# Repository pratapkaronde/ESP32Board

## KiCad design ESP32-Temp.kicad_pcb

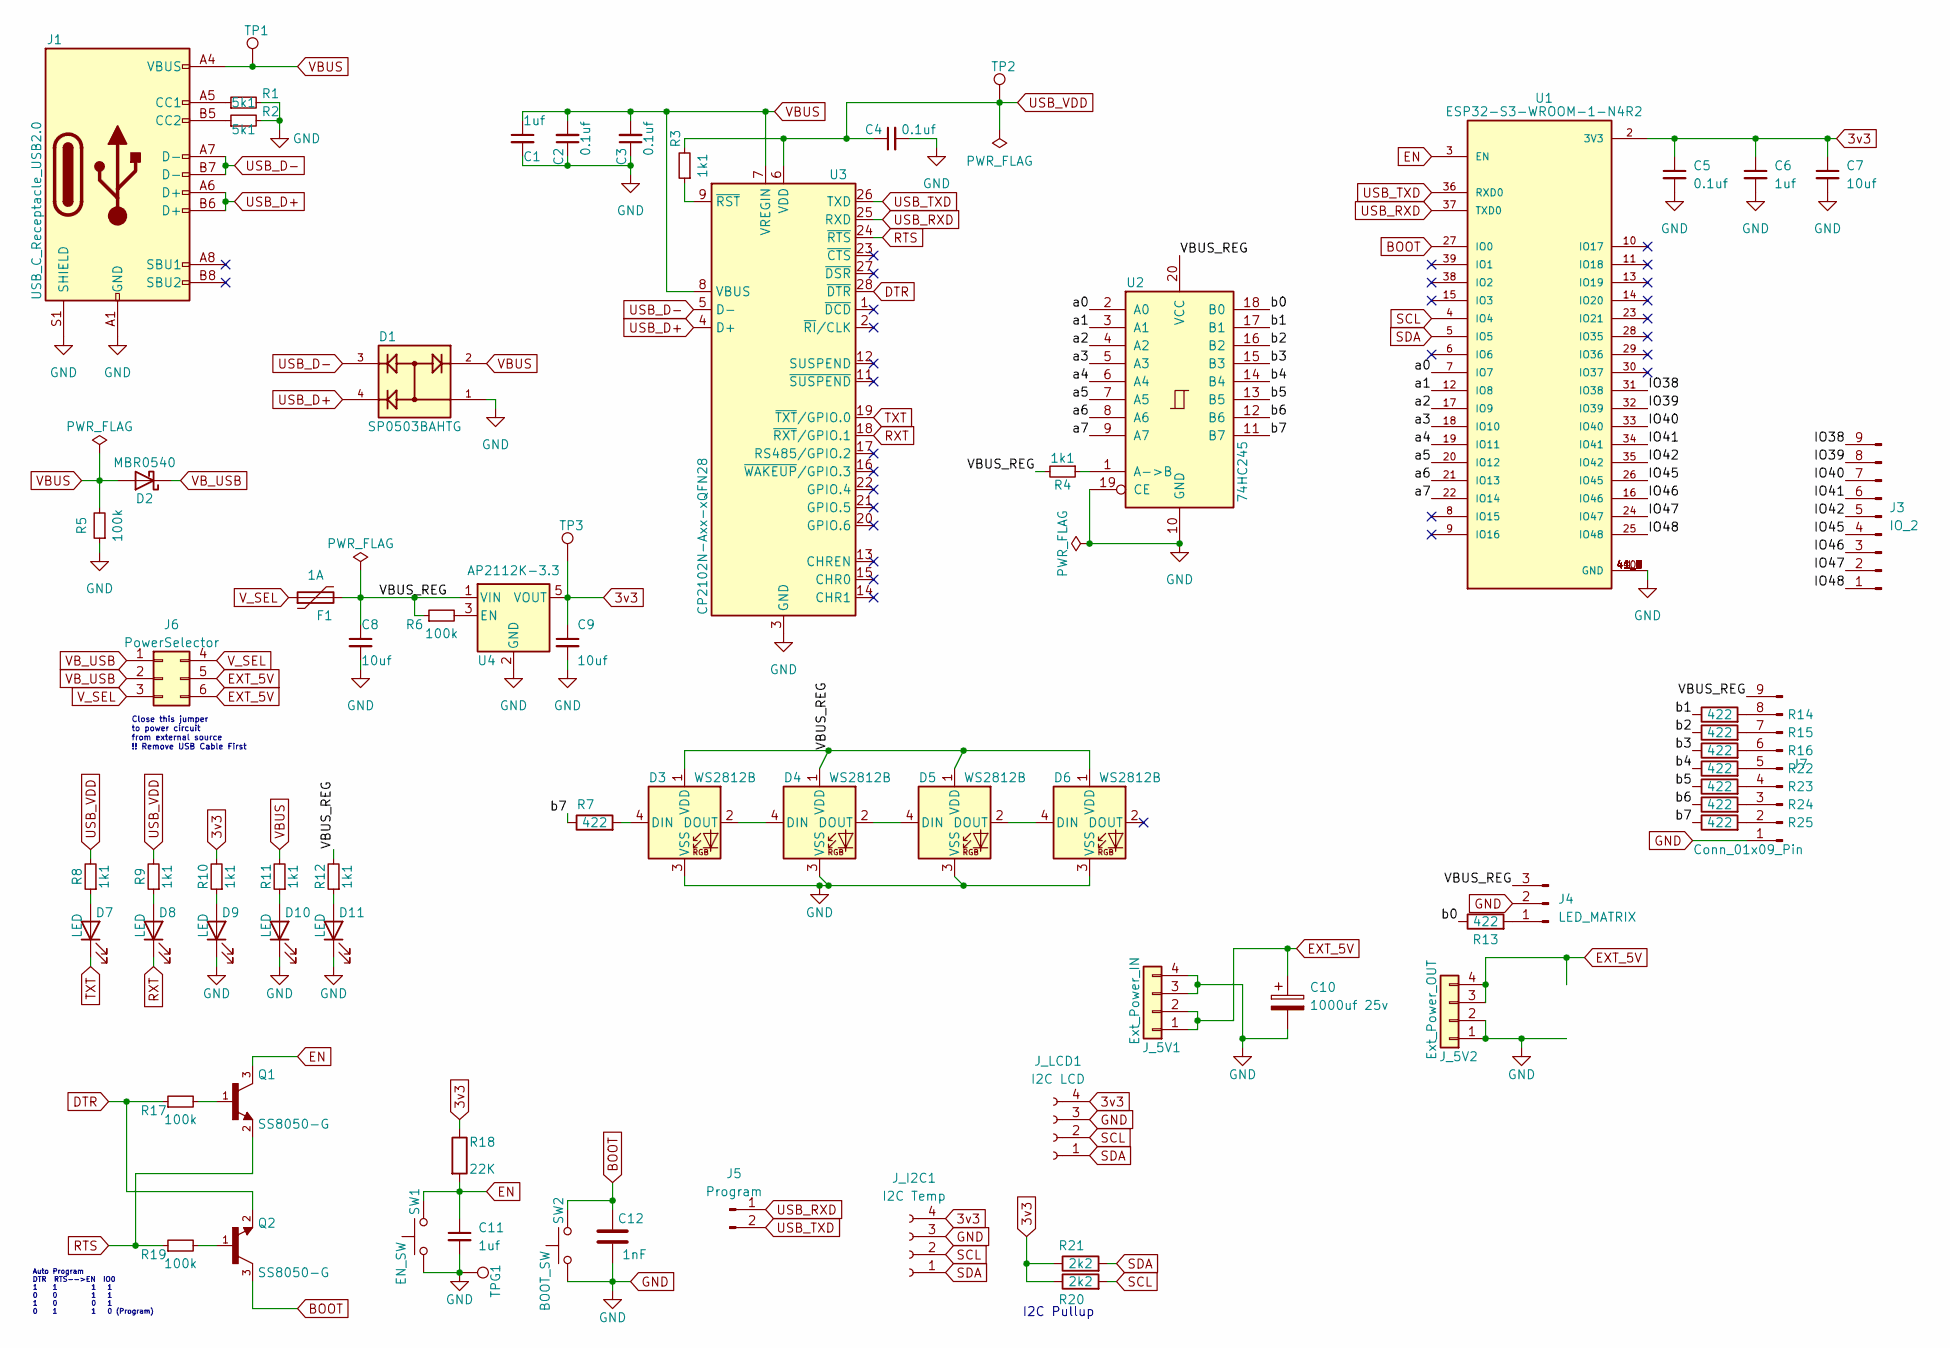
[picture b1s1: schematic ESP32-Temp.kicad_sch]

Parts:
C1, C6, C11: 1uf; C_0402_1005Metric; LCSC C14445
C2, C3, C4, C5: 0.1uf; C_0402_1005Metric; LCSC C56392
C7, C8, C9: 10uf; C_0402_1005Metric; LCSC C76991
C10: 1000uf 25v; CP_Radial_D10.0mm_P5.00mm
C12: 1nF; C_0402_1005Metric; LCSC C1523
D1: SP0503BAHTG; SOT143; PARTREV N/A; LCSC C3029025
D2: MBR0540; D_SOD-123; LCSC C116159
D3, D4, D5, D6: WS2812B; LED_WS2812B-2020_PLCC4_2.0x2.0mm; LCSC C2976072
D7, D8, D9, D10, D11: LED; LED_0402_1005Metric; LCSC C71911
F1: 1A; C_Disc_D5.0mm_W2.5mm_P2.50mm
J1: USB_C_Receptacle_USB2.0; USB_C_Receptacle_GCT_USB4105-xx-A_16P_TopMnt_Horizontal; LCSC C319148
J3: IO_2; PinHeader_1x09_P1.27mm_Vertical
J4: LED_MATRIX; PinHeader_1x03_P2.54mm_Vertical
J5: Program; PinHeader_1x02_P2.54mm_Vertical
J6: PowerSelector; PinHeader_2x03_P2.54mm_Vertical
J7: Conn_01x09_Pin; PinHeader_1x09_P2.54mm_Vertical
J_5V1: Ext_Power_IN; JST_EH_B4B-EH-A_1x04_P2.50mm_Vertical
J_5V2: Ext_Power_OUT; JST_EH_B4B-EH-A_1x04_P2.50mm_Vertical
J_I2C1: I2C Temp; PinHeader_1x04_P2.54mm_Vertical
J_LCD1: I2C LCD; PinHeader_1x04_P2.54mm_Vertical
Q1, Q2: SS8050-G; TRANS_SS8050-G; PARTREV A; LCSC C164885
R1, R2: 5k1; R_0402_1005Metric; LCSC C105872
R3, R4, R8, R9, R10, R11, R12: 1k1; R_0603_1608Metric; LCSC C22764
R5, R6: 100k; R_0603_1608Metric; LCSC C319969
R7, R13, R14, R15, R16, R22, R23, R24, R25: 422; R_Axial_DIN0204_L3.6mm_D1.6mm_P5.08mm_Horizontal
R17, R19: 100k; R_0402_1005Metric; LCSC C25741
R18: 22K; R_0402_1005Metric; LCSC C25768
R20, R21: 2k2; R_0402_1005Metric; LCSC C25879
SW1: EN_SW; SolderJumper-2_P1.3mm_Open_Pad1.0x1.5mm
SW2: BOOT_SW; SolderJumper-2_P1.3mm_Open_Pad1.0x1.5mm
TP1, TP2, TP3: TestPoint; TestPoint_THTPad_1.0x1.0mm_Drill0.5mm
TPG1: TestPoint; TestPoint_THTPad_1.0x1.0mm_Drill0.5mm
U1: ESP32-S3-WROOM-1-N4R2; XCVR_ESP32-S3-WROOM-1-N4R2; PARTREV v1.0; LCSC C2913203
U2: 74HC245; SOIC-20W_7.5x12.8mm_P1.27mm; LCSC C5625
U3: CP2102N-Axx-xQFN28; QFN-28-1EP_5x5mm_P0.5mm_EP3.35x3.35mm; LCSC C6568
U4: AP2112K-3.3; SOT-23-5; LCSC C3021085

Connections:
3v3: C5.1, C6.1, C7.1, C9.1, J_I2C1.4, J_LCD1.4, R10.2, R18.1, R20.1, R21.1, TP3.1, U1.2 (3V3), U4.5 (VOUT)
/IO38: J3.9, U1.31 (IO38)
/IO39: J3.8, U1.32 (IO39)
/IO40: J3.7, U1.33 (IO40)
/IO41: J3.6, U1.34 (IO41)
/IO42: J3.5, U1.35 (IO42)
/IO45: J3.4, U1.26 (IO45)
/IO46: J3.3, U1.16 (IO46)
/IO47: J3.2, U1.24 (IO47)
/IO48: J3.1, U1.25 (IO48)
/VBUS_REG: C8.1, D3.1 (VDD), D4.1 (VDD), D5.1 (VDD), D6.1 (VDD), F1.2, J4.3, J7.9, R4.2, R6.1, R12.2, U2.20 (VCC), U4.1 (VIN)
/a0: U1.7 (IO7), U2.2 (A0)
/a1: U1.12 (IO8), U2.3 (A1)
/a2: U1.17 (IO9), U2.4 (A2)
/a3: U1.18 (IO10), U2.5 (A3)
/a4: U1.19 (IO11), U2.6 (A4)
/a5: U1.20 (IO12), U2.7 (A5)
/a6: U1.21 (IO13), U2.8 (A6)
/a7: U1.22 (IO14), U2.9 (A7)
/b0: R13.1, U2.18 (B0)
/b1: R14.1, U2.17 (B1)
/b2: R15.1, U2.16 (B2)
/b3: R16.1, U2.15 (B3)
/b4: R22.1, U2.14 (B4)
/b5: R23.1, U2.13 (B5)
/b6: R24.1, U2.12 (B6)
/b7: R7.1, R25.1, U2.11 (B7)
BOOT: C12.1, Q2.3, SW2.2, U1.27 (IO0)
DTR: Q2.2, R17.1, U3.28 (~DTR)
EN: C11.1, Q1.3, R18.2, SW1.2, U1.3 (EN)
EXT_5V: C10.1, J6.5, J6.6, J_5V1.1, J_5V1.2, J_5V2.3, J_5V2.4
GND: C1.2, C2.1, C3.1, C4.2, C5.2, C6.2, C7.2, C8.2, C9.2, C10.2, C11.2, C12.2, D1.1, D3.3 (VSS), D4.3 (VSS), D5.3 (VSS), D6.3 (VSS), D9.1 (K), D10.1 (K), D11.1 (K), J1.A1 (GND), J1.A12 (GND), J1.B1 (GND), J1.B12 (GND), J1.S1 (SHIELD), J4.2, J7.1, J_5V1.3, J_5V1.4, J_5V2.1, J_5V2.2, J_I2C1.3, J_LCD1.3, R1.2, R2.2, R5.1, SW1.1, SW2.1, TPG1.1, U1.1 (GND), U1.40 (GND), U1.41_1 (GND), U1.41_2 (GND), U1.41_3 (GND), U1.41_4 (GND), U1.41_5 (GND), U1.41_6 (GND), U1.41_7 (GND), U1.41_8 (GND), U1.41_9 (GND), U2.10 (GND), U2.19 (CE), U3.3 (GND), U3.29 (GND), U4.2 (GND)
unnamed: D3.4 (DIN), R7.2
unnamed: D3.2 (DOUT), D4.4 (DIN)
unnamed: D4.2 (DOUT), D5.4 (DIN)
unnamed: D5.2 (DOUT), D6.4 (DIN)
unnamed: D7.2 (A), R8.1
unnamed: D8.2 (A), R9.1
unnamed: D9.2 (A), R10.1
unnamed: D10.2 (A), R11.1
unnamed: D11.2 (A), R12.1
unnamed: J1.A5 (CC1), R1.1
unnamed: J1.B5 (CC2), R2.1
unnamed: J4.1, R13.2
unnamed: J7.2, R25.2
unnamed: J7.3, R24.2
unnamed: J7.4, R23.2
unnamed: J7.5, R22.2
unnamed: J7.6, R16.2
unnamed: J7.7, R15.2
unnamed: J7.8, R14.2
unnamed: Q1.1, R17.2
unnamed: Q2.1, R19.2
unnamed: R4.1, U2.1 (A->B)
unnamed: R3.1, U3.9 (~RST)
unnamed: R6.2, U4.3 (EN)
RTS: Q1.2, R19.1, U3.24 (~RTS)
RXT: D8.1 (K), U3.18 (~RXT/GPIO.1)
SCL: J_I2C1.2, J_LCD1.2, R21.2, U1.4 (IO4)
SDA: J_I2C1.1, J_LCD1.1, R20.2, U1.5 (IO5)
TXT: D7.1 (K), U3.19 (~TXT/GPIO.0)
USB_D+: D1.4, J1.A6 (D+), J1.B6 (D+), U3.4 (D+)
USB_D-: D1.3, J1.A7 (D-), J1.B7 (D-), U3.5 (D-)
USB_RXD: J5.1, U1.37 (TXD0), U3.25 (RXD)
USB_TXD: J5.2, U1.36 (RXD0), U3.26 (TXD)
USB_VDD: C4.1, R3.2, R8.2, R9.2, TP2.1, U3.6 (VDD)
VBUS: C1.1, C2.2, C3.2, D1.2, D2.2 (A), J1.A4 (VBUS), J1.A9 (VBUS), J1.B4 (VBUS), J1.B9 (VBUS), R5.2, R11.2, TP1.1, U3.7 (VREGIN), U3.8 (VBUS)
VB_USB: D2.1 (K), J6.1, J6.2
V_SEL: F1.1, J6.3, J6.4

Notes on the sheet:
Close this jumper to power circuit from external source !! Remove USB Cable First
Auto Program DTR RTS-->EN IO0 1 1 1 1 0 0 1 1 1 0 0 1 0 1 1 0 (Program)
I2C Pullup

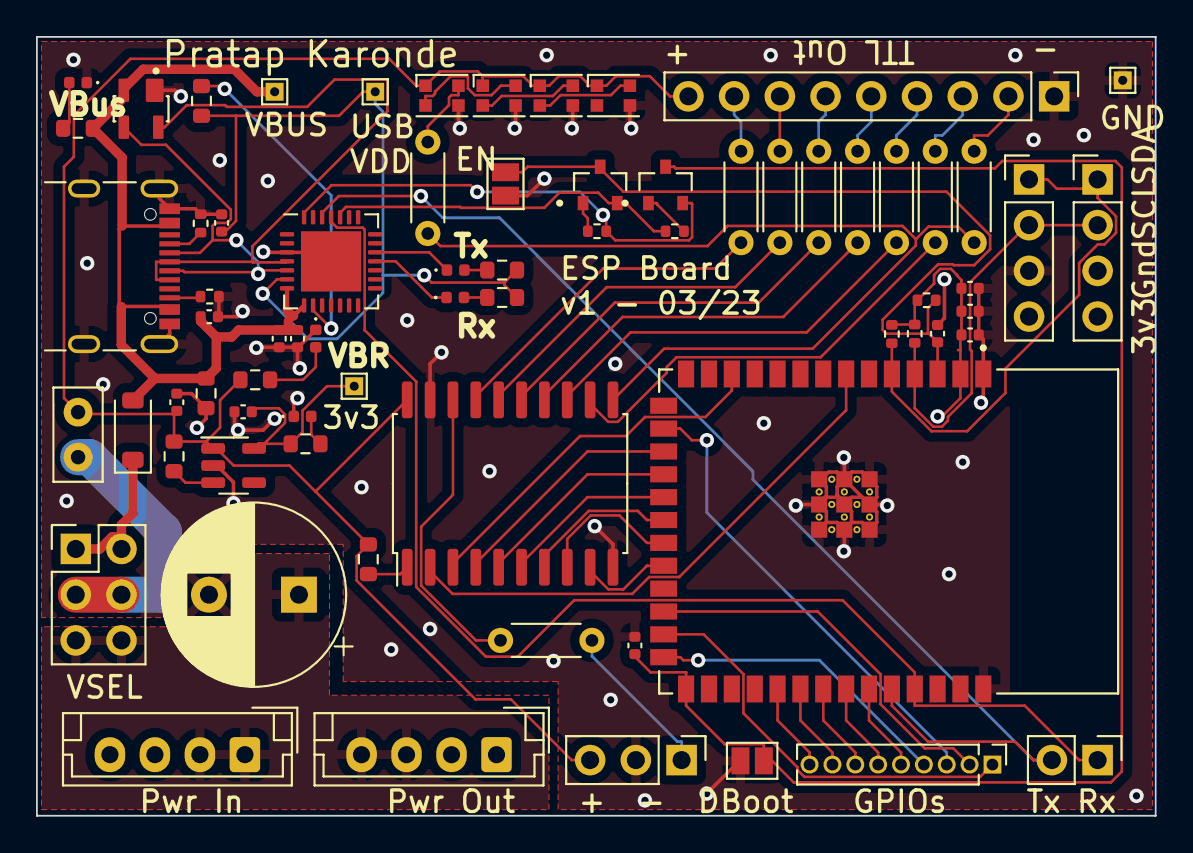
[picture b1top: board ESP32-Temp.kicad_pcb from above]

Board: 4 copper layers, 62.2 x 43.3 mm, 71 parts (0 on the bottom side), 69 nets.

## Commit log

2023-02-23 push
2023-03-16 JLCPCB Order
2023-03-18 JLCPCB Order again
